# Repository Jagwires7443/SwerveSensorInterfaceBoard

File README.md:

# SwerveSensorInterfaceBoard
Board to Interface an SRX MAG ENCODER to a SPARK MAX and a roboRIO

This small board (2.0" x 0.7") interfaces an SRX MAG ENCODER to a SPARK MAX (A/B incremental encoder inputs plus PWM absolute encoder input, although the latter is not yet supported by SPARK MAX) and to the roboRIO (PWM absolute encoder input used with a digital input; in software used with DutyCycle or DutyCycleEncoder).  The sensor is powered by the motor controller, and the roboRIO is properly isolated.  This is a good starting point for similar interface projects in the FRC (FIRST Robotics Competition) ecosystem.

These are the [KiCad](https://www.kicad.org/) design files, including schematic symbols, PCB footprints, and 3-D models for all the components.

***Note that a simpler way to handle this is to leave the SPARK MAX out of things and to simply connect pins 2 (+5V), 9 (PWM), and 10 (GND) from the SRX MAG ENCODER to a roboRIO digital input.  Indeed, until REV addresses [this](https://trello.com/c/bvnPPcZD/108-add-continuous-pid-capability) bug (fixed for 2023), there's not much point in trying to use the SPARK MAX to directly handle closed-loop control.  Here are links to parts (multiple suppliers) that are helpful with this approach:
[CABLE ASSEM .05" 10POS 3"](https://www.digikey.com/en/products/detail/samtec-inc/FFSD-05-D-03-00-01-N/2651110),
[10-pin 2x5 Socket-Socket 1.27mm IDC (SWD) Cable - 150mm long](https://www.adafruit.com/product/1675),
[SRX / Gadgeteer Data Cable (4-pack)](https://newsite.ctr-electronics.com/srx-gadgeteer-data-cable-4-pack/),
[Talon SRX / Spark Max - 10 Pin Data Cable](https://www.andymark.com/products/talon-srx-hero-10-pin-data-cable),
[SWD (2x5 1.27mm) Cable Breakout Board](https://www.adafruit.com/product/2743),
[Gadgeteer Breakout Module (5 Pack)](https://newsite.ctr-electronics.com/gadgeteer-breakout-module-5-pack/),
[SPARK MAX Data Port Breakout Board](https://www.revrobotics.com/rev-11-1278/).***

***Also note that REV now uses pin 6 of the SPARK MAX data port for the PWM absolute encoder input, so this part of the PCB desgn is also out-of-date.***

Working with the 0.05" headers and fine-pitch cables can be tough.  Test that the motor runs as expected before connecting to the SPARK MAX.  Then, be sure the SPARK MAX has been configured to "Alternate Encoder Mode" and this configuration has been saved.  At this point, connect to the SPARK MAX and verify that the LED on the SRX MAG ENCODER is on (any color, the color only depends on the distance to the magnet).  Be sure the LEDs on the SPARK MAX are as expected, and that you can still communicate with it via "REV Hardware Client".  If not, power down and start looking for shorts or opens -- likely trouble spots are the solder connections on the board and the points where the connectors and cables join.  At this point, power and ground are probably good.

Now, check that the motor still runs as expected.  It is possible to short signals which are essential for the motor to run, so suspect a problem in this area if the motor no longer runs well.  Even though these signals normally come in via the built-in signal cable from the (NEO) motor, these same connections are present at the "Data Port".  Trouble in this area may also cause a "Sensor Fault".  If things are all good so far, you can run the motor and should see changing values returned via GetPosition() and GetVelocity().  Finally, check the PWM absolute position signal using a DutyCycle object.  Code to do these things is [here](https://github.com/Jagwires7443/Swerve).  This code contains an extensive test mode (used with Shuffleboard) which will read and display all of the sensor data.

Another option for this type of board is to go surface mount.  The boards REV itself has created seem to use an [FLE-107-01-G-DV](https://www.samtec.com/products/fle-107-01-g-dv-a-tr) connector to directly plug into the SPARK MAX.  Note this is actually a 14-pin connector -- the outer 4 pins are not used to make a connection, but to help to take up some of the excess space on each side of the 10 pins on the connector that is part of the SPARK MAX.  The REV boards are shaped to match the outline of the end of the SPARK MAX where they plug in (roughly 1.16" wide by 0.75" to 0.90" tall, with a roughtly 0.14" by 0.25" notch on each side, roughly 0.14" from the top, with the connector centered roughly 0.18" below the bottom of the notch).

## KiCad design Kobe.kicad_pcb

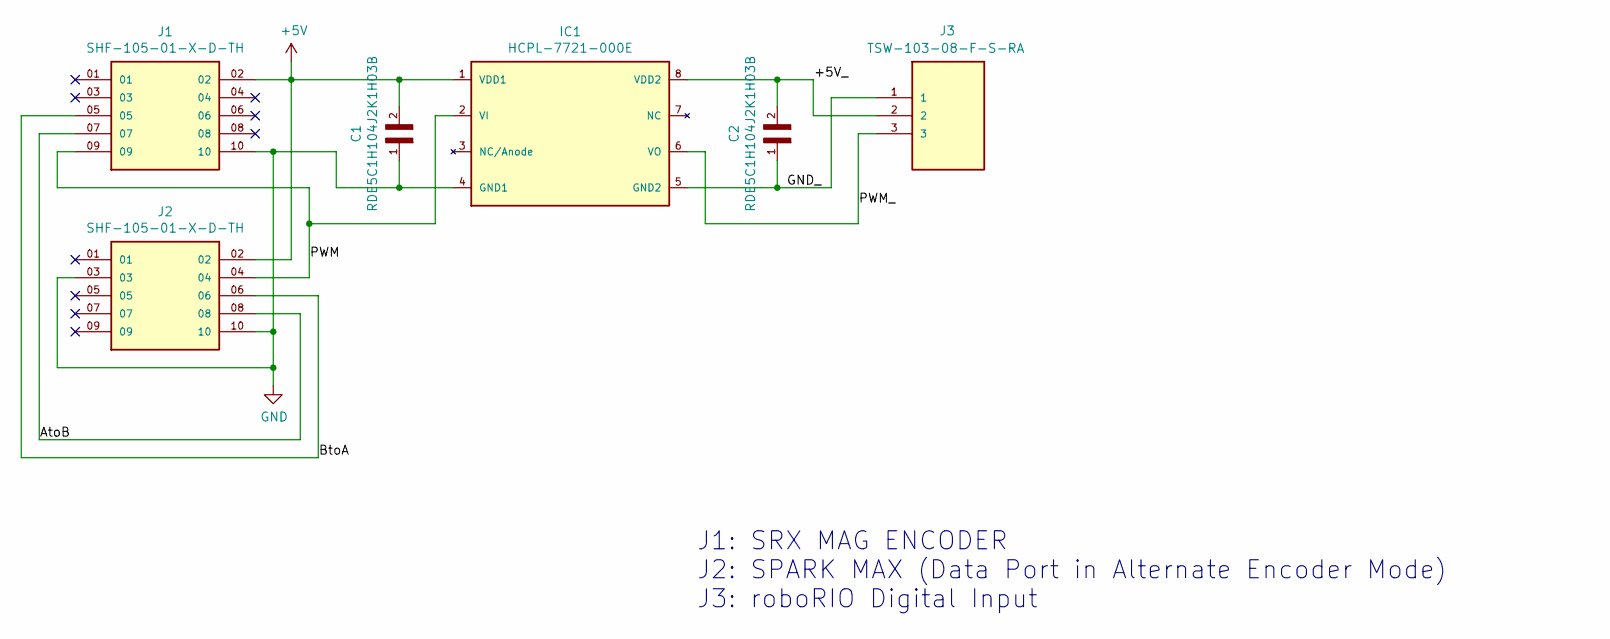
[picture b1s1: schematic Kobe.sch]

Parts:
C1, C2: RDE5C1H104J2K1H03B; CAP_RDE5C1H104J2K1H03B
IC1: HCPL-7721-000E; DIL08; MPN HCPL-7721-000EA-000E
J1, J2: SHF-105-01-X-D-TH; SAMTEC_SHF-105-01-X-D-TH; PARTREV A
J3: TSW-103-08-F-S-RA

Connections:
+5V: C1.2, IC1.1 (VDD1), J1.02, J2.02
/+5V_: C2.2, IC1.8 (VDD2), J3.2
/AtoB: J1.07, J2.08
/BtoA: J1.05, J2.06
/GND_: C2.1, IC1.5 (GND2), J3.1
/PWM: IC1.2 (VI), J1.09, J2.04
/PWM_: IC1.6 (VO), J3.3
GND: C1.1, IC1.4 (GND1), J1.10, J2.03, J2.10

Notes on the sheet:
J1: SRX MAG ENCODER J2: SPARK MAX (Data Port in Alternate Encoder Mode) J3: roboRIO Digital Input

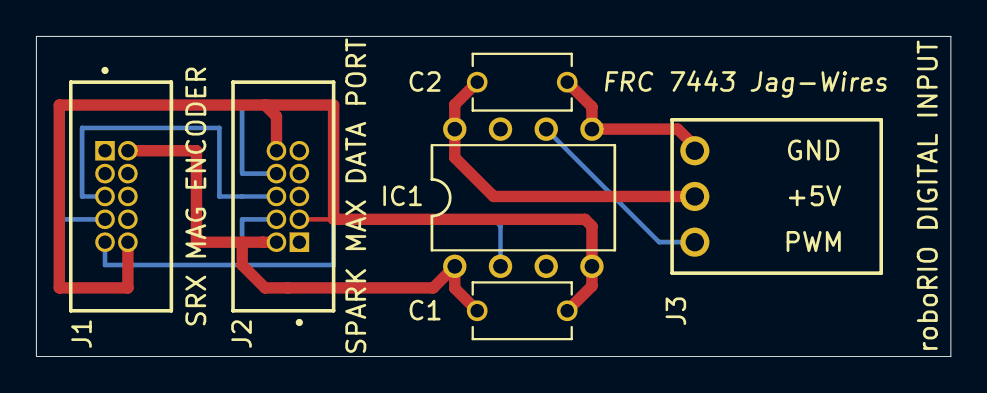
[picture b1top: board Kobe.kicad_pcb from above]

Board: 2 copper layers, 50.8 x 17.8 mm, 6 parts (0 on the bottom side), 8 nets.

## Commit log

2021-07-29 Initial Upload
2021-07-29 Images for README
2021-08-06 Update README.md
    Call out an issue in using SPARK MAX for closed-loop control when the A/B encoder needs to wrap around periodically.
